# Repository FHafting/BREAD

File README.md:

# BREAD
This project is fully documented in the paper: Shane Oberloier, Nicholas G. Whisman, Finn Hafting, Joshua M. Pearce, Open Source Framework for a Broadly Expandable and Reconfigurable Data Acquisition and Automation Device (BREAD), ''HardwareX'', 2023, e00467, https://doi.org/10.1016/j.ohx.2023.e00467.

All case designs can be found on Onshape: https://cad.onshape.com/documents/f4c13a5c0b1f8d88ed1f5752/w/29d0c0346ddaeb06e16ff42f/e/1077373224ada363d171e3fe?renderMode=0&uiState=65d3aad45b82c32cb51ae4c9

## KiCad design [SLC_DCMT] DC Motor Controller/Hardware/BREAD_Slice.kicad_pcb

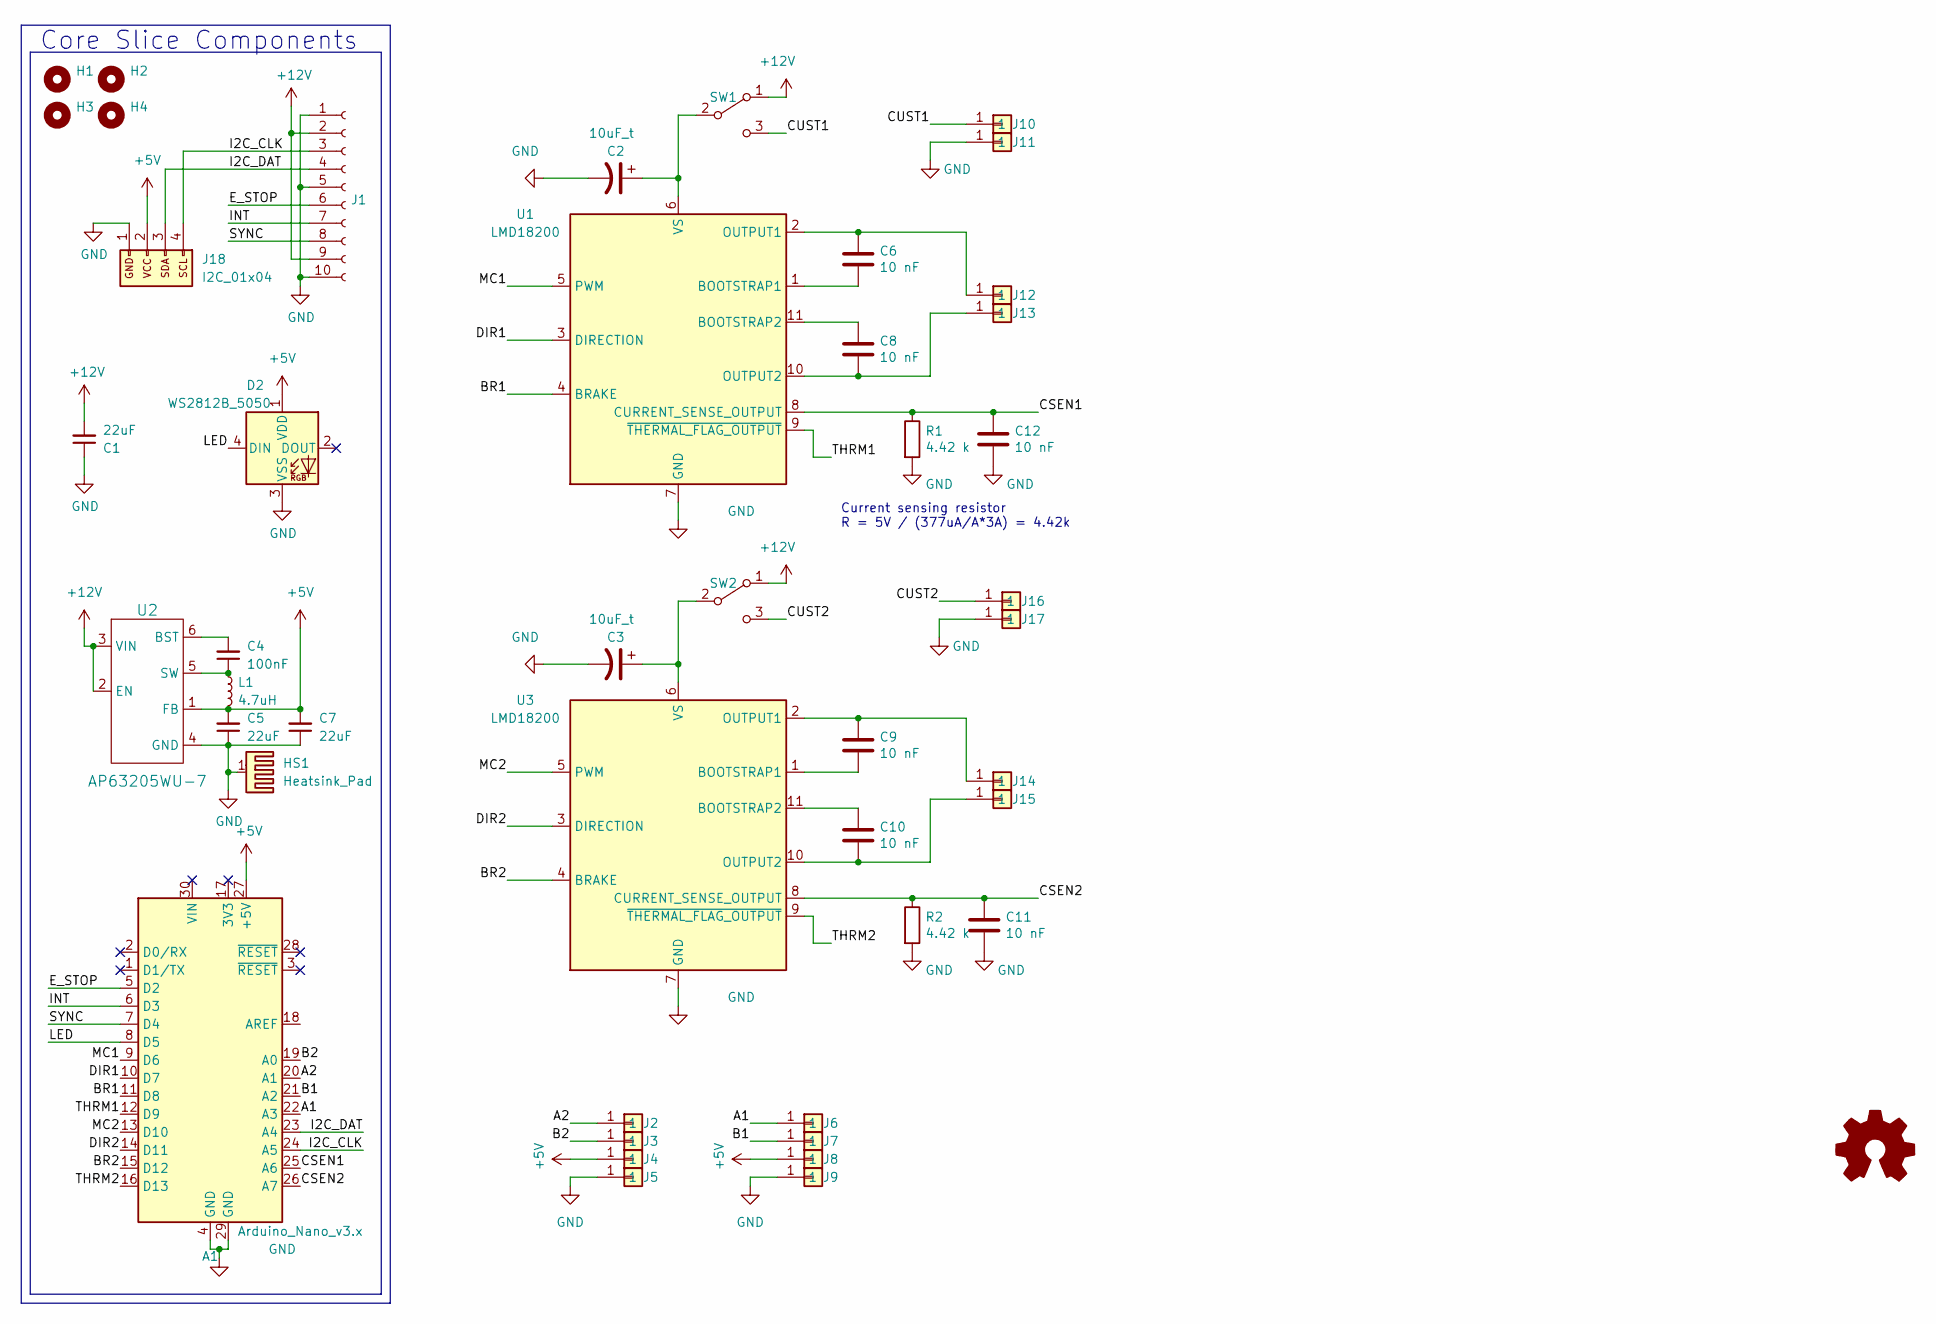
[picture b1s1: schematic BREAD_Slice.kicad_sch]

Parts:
A1: Arduino_Nano_v3.x; Arduino_Nano
C1, C5, C7: 22uF; C_1206_3216Metric
C2, C3: 10uF_t; C_1206_3216Metric; Part # T491C106K025AT
C4: 100nF; C_1206_3216Metric
C6, C8, C9, C10, C11, C12: 10 nF; C_1206_3216Metric_Pad1.33x1.80mm_HandSolder
D2: WS2812B_5050; WS2812-5050-4PIN
H1, H2, H3, H4: MountingHole; MountingHole_5mm
HS1: Heatsink_Pad; Thermal Pad
J1: Conn_01x10_Female; PinSocket_1x10_P2.54mm_Horizontal
J2, J3, J4, J5, J7, J8, J9: Term_PressFit_Phoenix_Contact; Term_PressFit_3.5mm_H_PC
J6: Term_PressFit_Phoenix_Contact; Term_PressFit_3.5mm_H_ENDCAP_PC
J10, J11, J13, J15, J16, J17: Term_PressFit_Phoenix_Contact; Term_PressFit_5mm_H_PC
J12, J14: Term_PressFit_Phoenix_Contact; Term_PressFit_5mm_H_ENDCAP_PC
J18: I2C_01x04; JST_SH_SM04B-SRSS-TB_1x04-1MP_P1.00mm_Horizontal
L1: 4.7uH; L_1210_3225Metric
Logo1: Logo_Open_Hardware_Small; OSHW-Symbol_6.7x6mm_SilkScreen
R1, R2: 4.42 k; R_1206_3216Metric_Pad1.30x1.75mm_HandSolder
SW1, SW2: SW_SPDT; L102011MS02Q
U1, U3: LMD18200; TO-220-11_P3.4x5.08mm_StaggerOdd_Lead4.85mm_Vertical
U2: AP63205WU-7; TSOT-23-6

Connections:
+5V: A1.27 (+5V), C5.2, C7.2, D2.1 (VDD), J4.1, J8.1, J18.2, L1.2, U2.1 (FB)
+12V: C1.2, J1.2, J1.9, SW1.1 (A), SW2.1 (A), U2.2 (EN), U2.3 (VIN)
/A1: A1.22 (A3), J6.1
/A2: A1.20 (A1), J2.1
/B1: A1.21 (A2), J7.1
/B2: A1.19 (A0), J3.1
/BR1: A1.11 (D8), U1.4 (BRAKE)
/BR2: A1.15 (D12), U3.4 (BRAKE)
/CSEN1: A1.25 (A6), C12.1, R1.1, U1.8 (CURRENT_SENSE_OUTPUT)
/CSEN2: A1.26 (A7), C11.1, R2.1, U3.8 (CURRENT_SENSE_OUTPUT)
/CUST1: J10.1, SW1.3 (C)
/CUST2: J16.1, SW2.3 (C)
/DIR1: A1.10 (D7), U1.3 (DIRECTION)
/DIR2: A1.14 (D11), U3.3 (DIRECTION)
/E_STOP: A1.5 (D2), J1.6
/I2C_CLK: A1.24 (A5), J1.3, J18.4
/I2C_DAT: A1.23 (A4), J1.4, J18.3
/INT: A1.6 (D3), J1.7
/LED: A1.8 (D5), D2.4 (DIN)
/MC1: A1.9 (D6), U1.5 (PWM)
/MC2: A1.13 (D10), U3.5 (PWM)
/SYNC: A1.7 (D4), J1.8
/THRM1: A1.12 (D9), U1.9 (~THERMAL_FLAG_OUTPUT)
/THRM2: A1.16 (D13), U3.9 (~THERMAL_FLAG_OUTPUT)
GND: A1.4 (GND), A1.29 (GND), C1.1, C2.2, C3.2, C5.1, C7.1, C11.2, C12.2, D2.3 (VSS), HS1.1, J1.1, J1.5, J1.10, J5.1, J9.1, J11.1, J17.1, J18.1, R1.2, R2.2, U1.7 (GND), U2.4 (GND), U3.7 (GND)
unnamed: C2.1, SW1.2 (B), U1.6 (VS)
unnamed: C3.1, SW2.2 (B), U3.6 (VS)
unnamed: C6.2, U1.1 (BOOTSTRAP1)
unnamed: C8.1, U1.11 (BOOTSTRAP2)
unnamed: C6.1, J12.1, U1.2 (OUTPUT1)
unnamed: C8.2, J13.1, U1.10 (OUTPUT2)
unnamed: C4.2, U2.6 (BST)
unnamed: C4.1, L1.1, U2.5 (SW)
unnamed: C9.2, U3.1 (BOOTSTRAP1)
unnamed: C10.1, U3.11 (BOOTSTRAP2)
unnamed: C9.1, J14.1, U3.2 (OUTPUT1)
unnamed: C10.2, J15.1, U3.10 (OUTPUT2)

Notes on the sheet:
Current sensing resistor R = 5V / (377uA/A*3A) = 4.42k
Core Slice Components

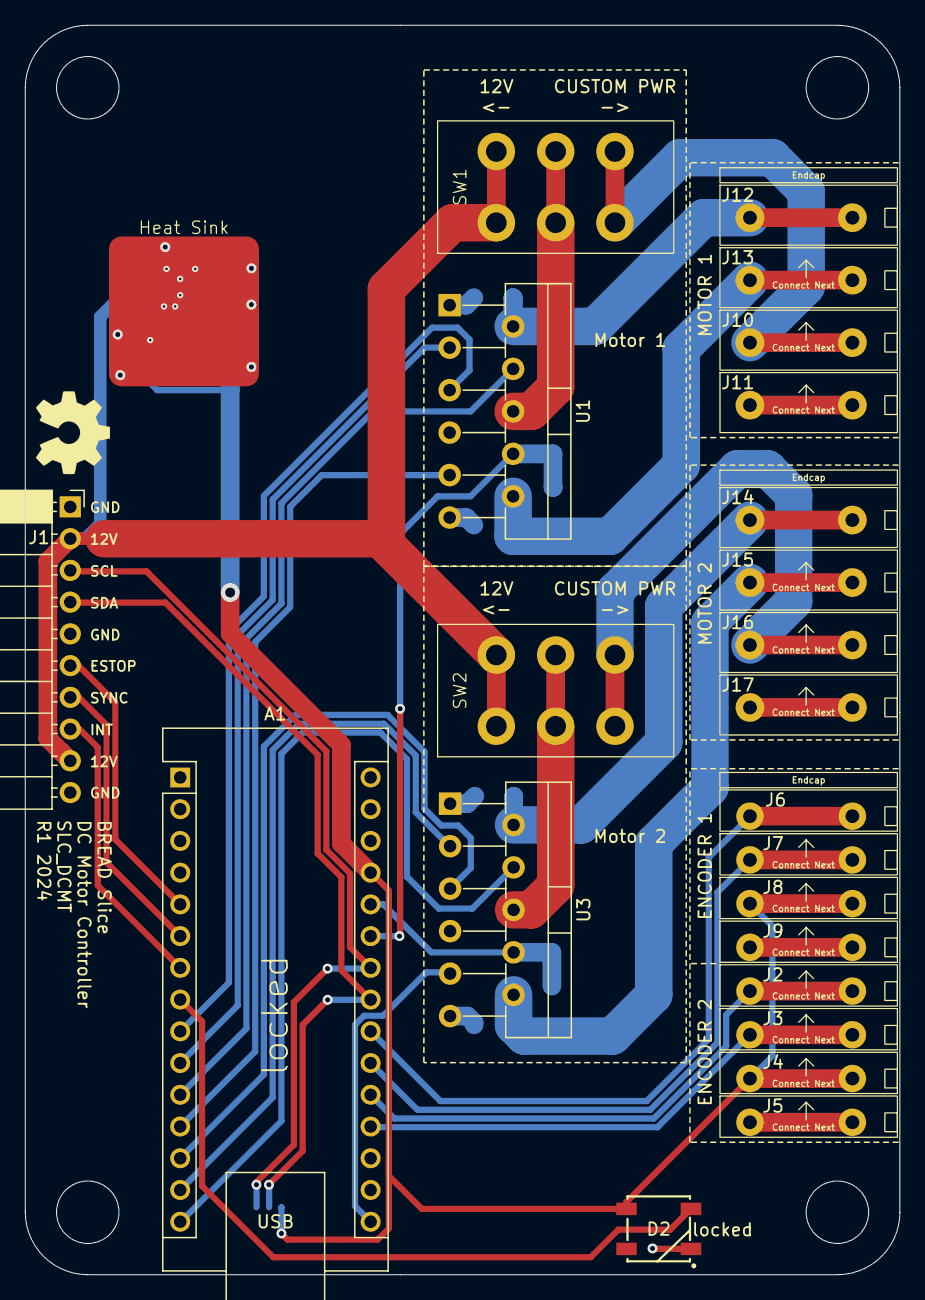
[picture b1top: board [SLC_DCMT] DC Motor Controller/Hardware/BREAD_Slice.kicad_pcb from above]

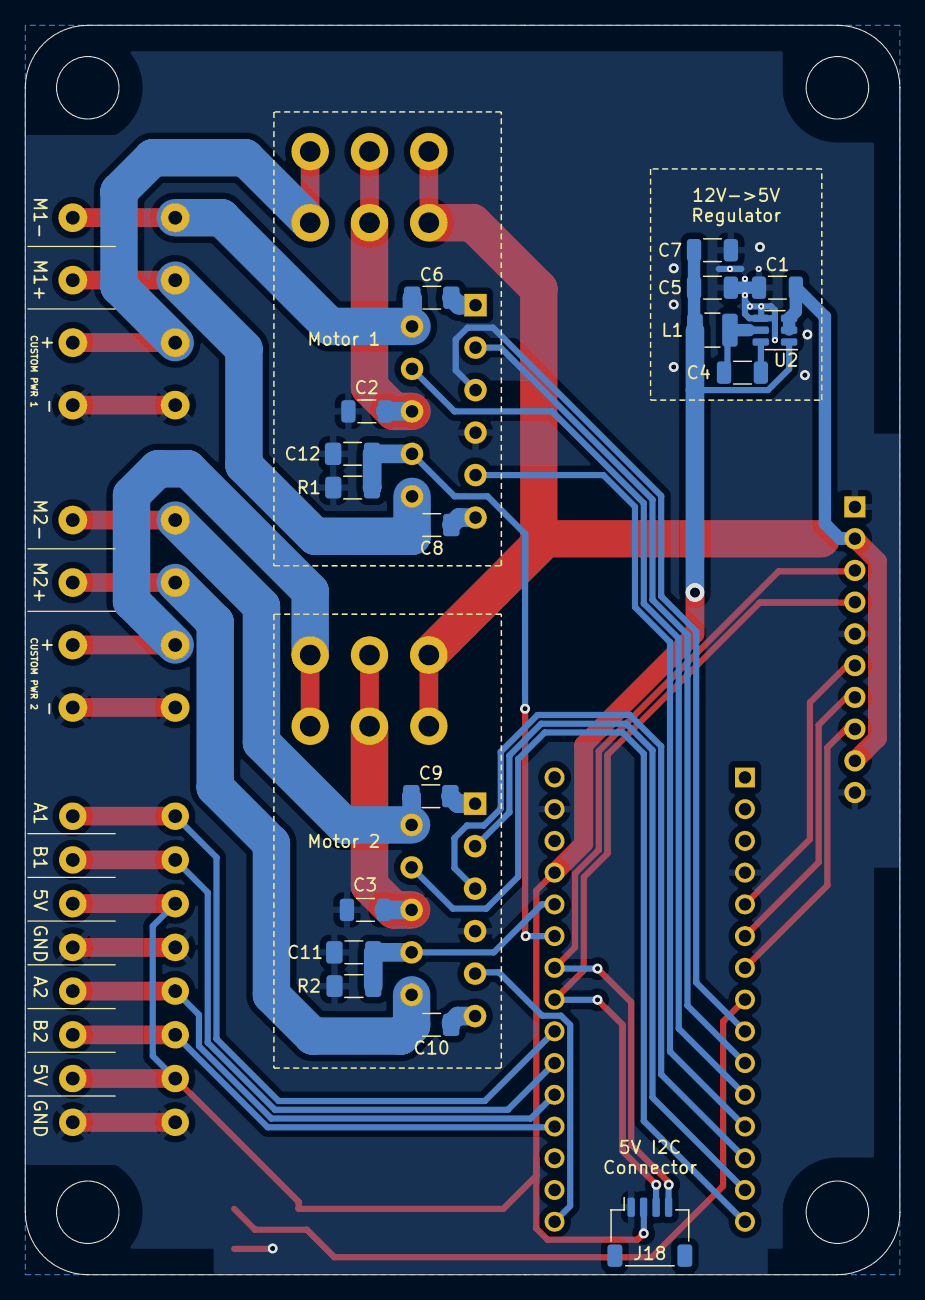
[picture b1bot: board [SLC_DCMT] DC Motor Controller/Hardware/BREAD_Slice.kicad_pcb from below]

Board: 2 copper layers, 70.0 x 100.0 mm, 46 parts (17 on the bottom side), 37 nets.

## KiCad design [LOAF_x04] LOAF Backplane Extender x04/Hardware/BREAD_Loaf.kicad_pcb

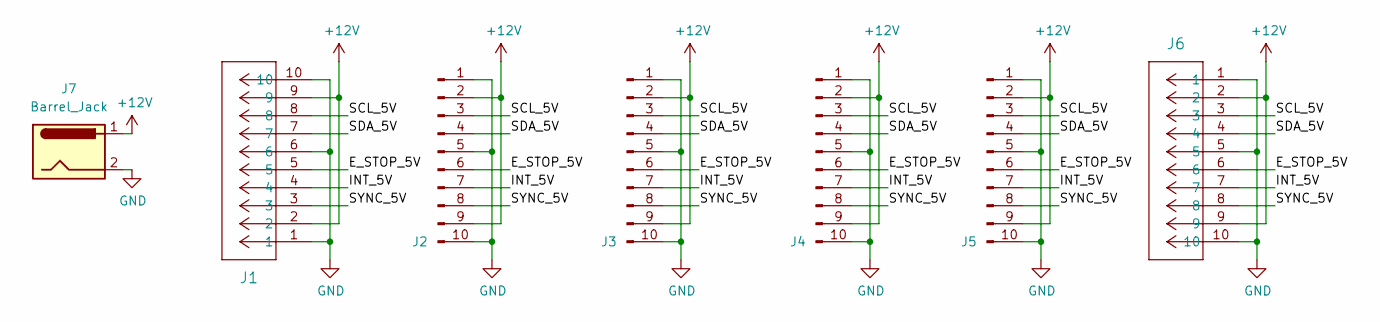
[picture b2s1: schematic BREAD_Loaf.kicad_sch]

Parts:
J1: PPPC101LGBN-RC; 1x10 RA Male Header 2.54mm Pitch
J2, J3, J4, J5: Conn_01x10_Male; BREAD 10-Pin Connector
J6: PPPC101LGBN-RC; PinSocket_1x10_P2.54mm_Horizontal
J7: Barrel_Jack; BarrelJack_CUI_PJ-063AH_Horizontal

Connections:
+12V: J1.2, J1.9, J2.2, J2.9, J3.2, J3.9, J4.2, J4.9, J5.2, J5.9, J6.2, J6.9, J7.1
/E_STOP_5V: J1.5, J2.6, J3.6, J4.6, J5.6, J6.6
/INT_5V: J1.4, J2.7, J3.7, J4.7, J5.7, J6.7
/SCL_5V: J1.8, J2.3, J3.3, J4.3, J5.3, J6.3
/SDA_5V: J1.7, J2.4, J3.4, J4.4, J5.4, J6.4
/SYNC_5V: J1.3, J2.8, J3.8, J4.8, J5.8, J6.8
GND: J1.1, J1.6, J1.10, J2.1, J2.5, J2.10, J3.1, J3.5, J3.10, J4.1, J4.5, J4.10, J5.1, J5.5, J5.10, J6.1, J6.5, J6.10, J7.2

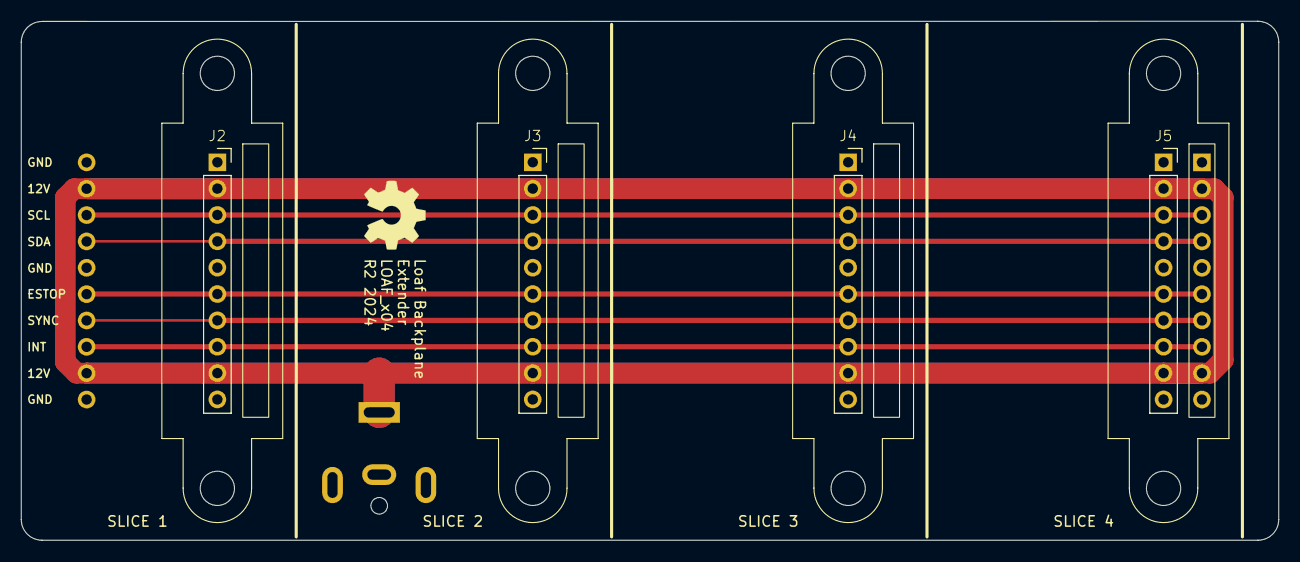
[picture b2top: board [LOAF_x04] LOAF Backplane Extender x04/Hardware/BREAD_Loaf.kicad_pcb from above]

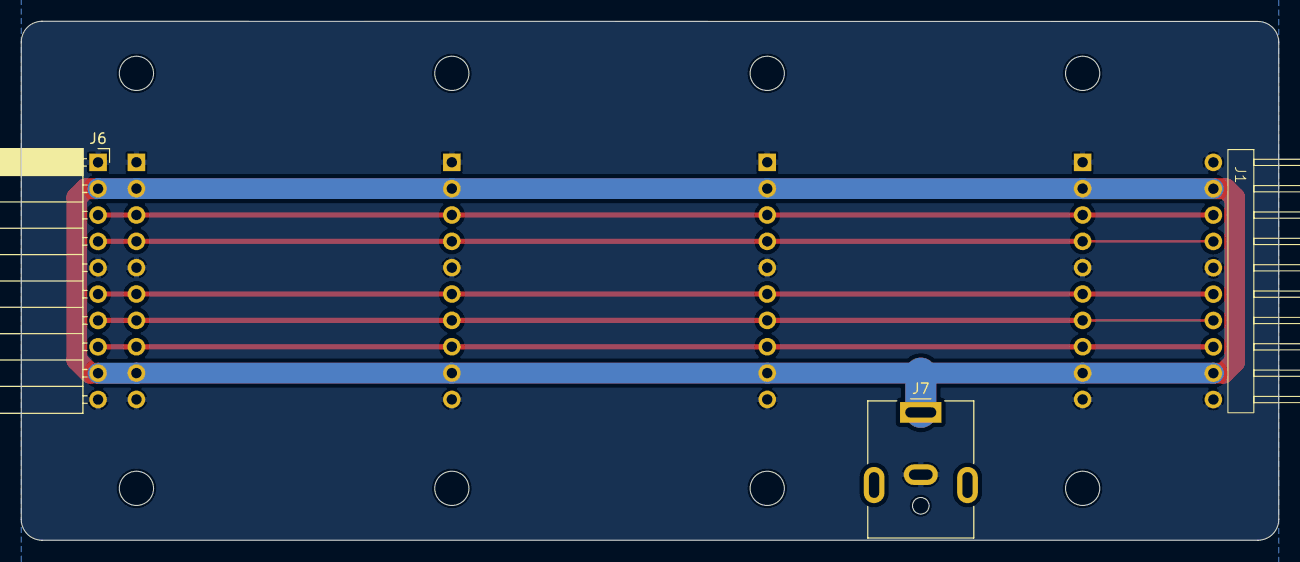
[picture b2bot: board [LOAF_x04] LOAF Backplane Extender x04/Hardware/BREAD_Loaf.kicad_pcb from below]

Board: 2 copper layers, 121.2 x 50.0 mm, 8 parts (3 on the bottom side), 7 nets.

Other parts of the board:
Logo1: Logo_Open_Hardware_Small; OSHW-Symbol_6.7x6mm_SilkScreen

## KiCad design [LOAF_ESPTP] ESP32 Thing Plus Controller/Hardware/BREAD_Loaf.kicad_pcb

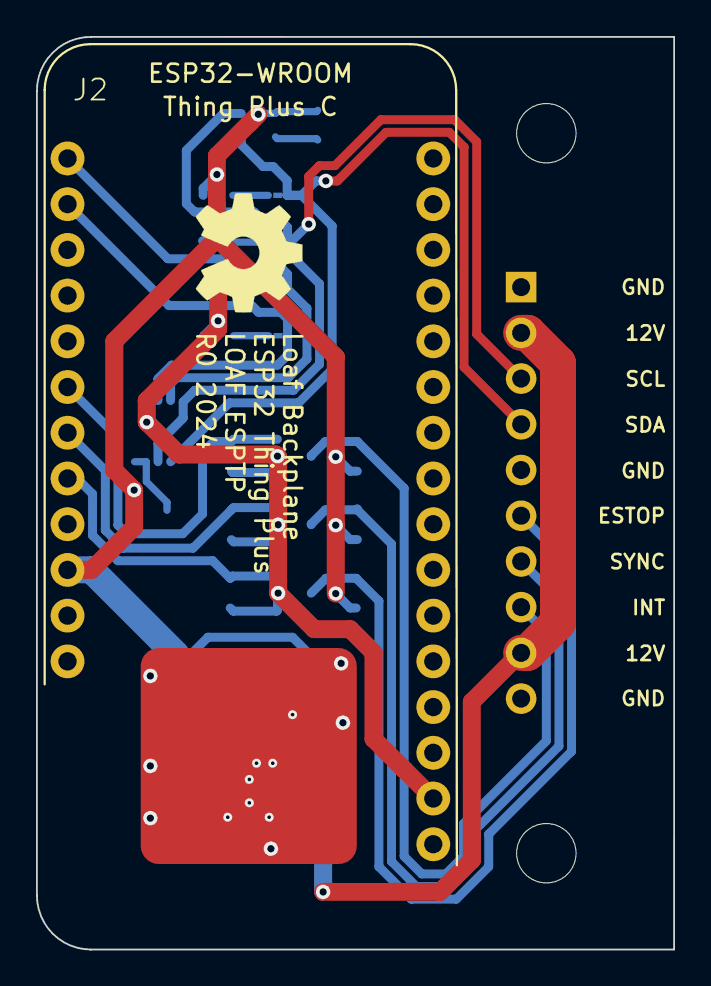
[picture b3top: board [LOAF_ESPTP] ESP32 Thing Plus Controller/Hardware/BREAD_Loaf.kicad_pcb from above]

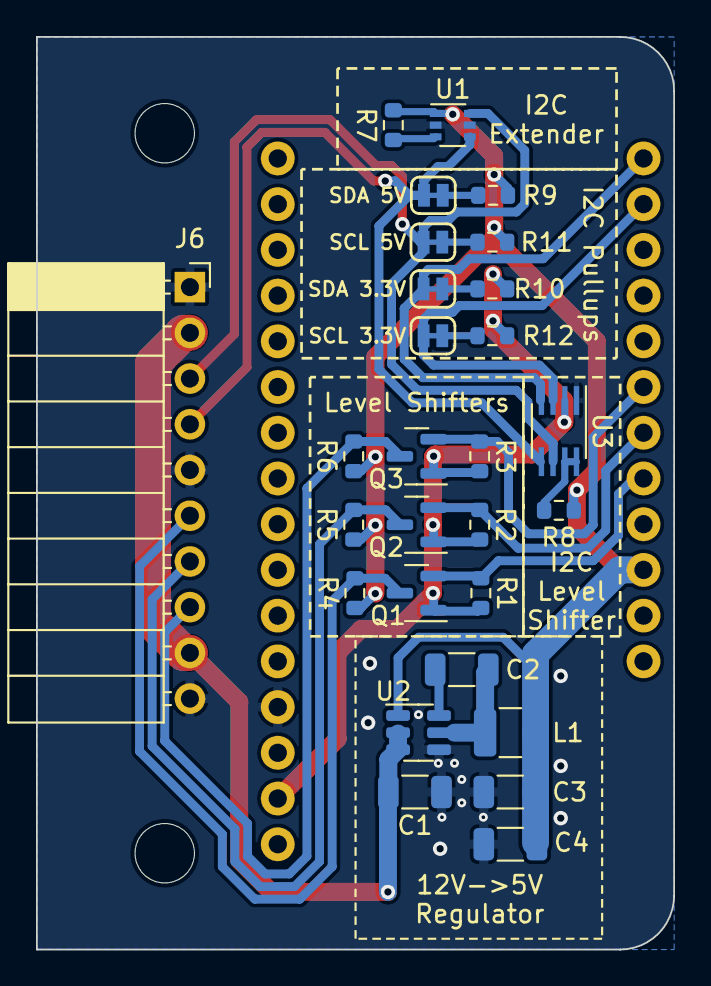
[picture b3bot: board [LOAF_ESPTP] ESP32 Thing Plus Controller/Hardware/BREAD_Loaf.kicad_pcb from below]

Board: 2 copper layers, 35.4 x 50.7 mm, 33 parts (28 on the bottom side), 22 nets.

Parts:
C1, C3, C4: 22uF; C_1206_3216Metric
C2: 100nF; C_1206_3216Metric
HS1: Heatsink_Pad; Thermal Pad
J2: THING_PLUS_LOGICAL; ESP_THING_PLUS
J6: PPPC101LGBN-RC; PinSocket_1x10_P2.54mm_Horizontal
JP1, JP2, JP3, JP4: SMT-JUMPER_2_NC_TRACE_SILK
L1: 4.7uH; L_1210_3225Metric
Logo1: Logo_Open_Hardware_Small; OSHW-Symbol_6.7x6mm_SilkScreen
Q1, Q2, Q3: BSS138; SOT-23
R1, R2, R3, R4, R5, R6, R7: 10k; R_0603_1608Metric
R8: 200k; R_0603_1608Metric
R9, R11: 4.7k; R_0603_1608Metric
R10, R12: 2.2k; R_0603_1608Metric
ST1, ST2: Stand_off; STAND-OFF
U1: LTC4311ISC6-TRMPBF; SOT-363_SC-70-6
U2: AP63205WU-7; TSOT-23-6
U3: PCA9306; SSOP-8_2.95x2.8mm_P0.65mm

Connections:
+3.3V: J2.27 (3.3V), Q1.1 (G), Q2.1 (G), Q3.1 (G), R1.2, R2.2, R3.2, R10.1, R12.1, U3.2 (VREF1)
+5V: C3.2, C4.2, J2.10 (V_USB), L1.2, R4.2, R5.2, R6.2, R7.1, R8.2, R9.1, R11.1, U1.1 (VCC), U2.1 (FB)
+12V: C1.2, J6.2, J6.9, U2.2 (EN), U2.3 (VIN)
/E_STOP_3.3V: J2.8 (GPIO1), Q1.2 (S), R1.1
/E_STOP_5V: J6.6, Q1.3 (D), R4.1
/INT_3.3V: J2.7 (GPIO2), Q2.2 (S), R2.1
/INT_5V: J6.7, Q2.3 (D), R5.1
/SCL_3.3V: J2.2 (SCL), JP4.2 (B), U3.3 (SCL1)
/SCL_5V: J6.3, JP2.2 (B), U1.6 (BUS1), U3.6 (SCL2)
/SDA_3.3V: J2.1 (SDA), JP3.2 (B), U3.4 (SDA1)
/SDA_5V: J6.4, JP1.2 (B), U1.4 (BUS2), U3.5 (SDA2)
/SYNC_3.3V: J2.6 (GPIO3), Q3.2 (S), R3.1
/SYNC_5V: J6.8, Q3.3 (D), R6.1
GND: C1.1, C3.1, C4.1, HS1.1, J2.25 (GND), J6.1, J6.5, J6.10, U1.2 (GND), U1.5 (GND), U2.4 (GND), U3.1 (GND)
unnamed: JP1.1 (A), R9.2
unnamed: JP2.1 (A), R11.2
unnamed: JP3.1 (A), R10.2
unnamed: JP4.1 (A), R12.2
unnamed: R7.2, U1.3 (ENABLE)
unnamed: C2.2, U2.6 (BST)
unnamed: C2.1, L1.1, U2.5 (SW)
unnamed: R8.1, U3.7 (VREF2), U3.8 (EN)

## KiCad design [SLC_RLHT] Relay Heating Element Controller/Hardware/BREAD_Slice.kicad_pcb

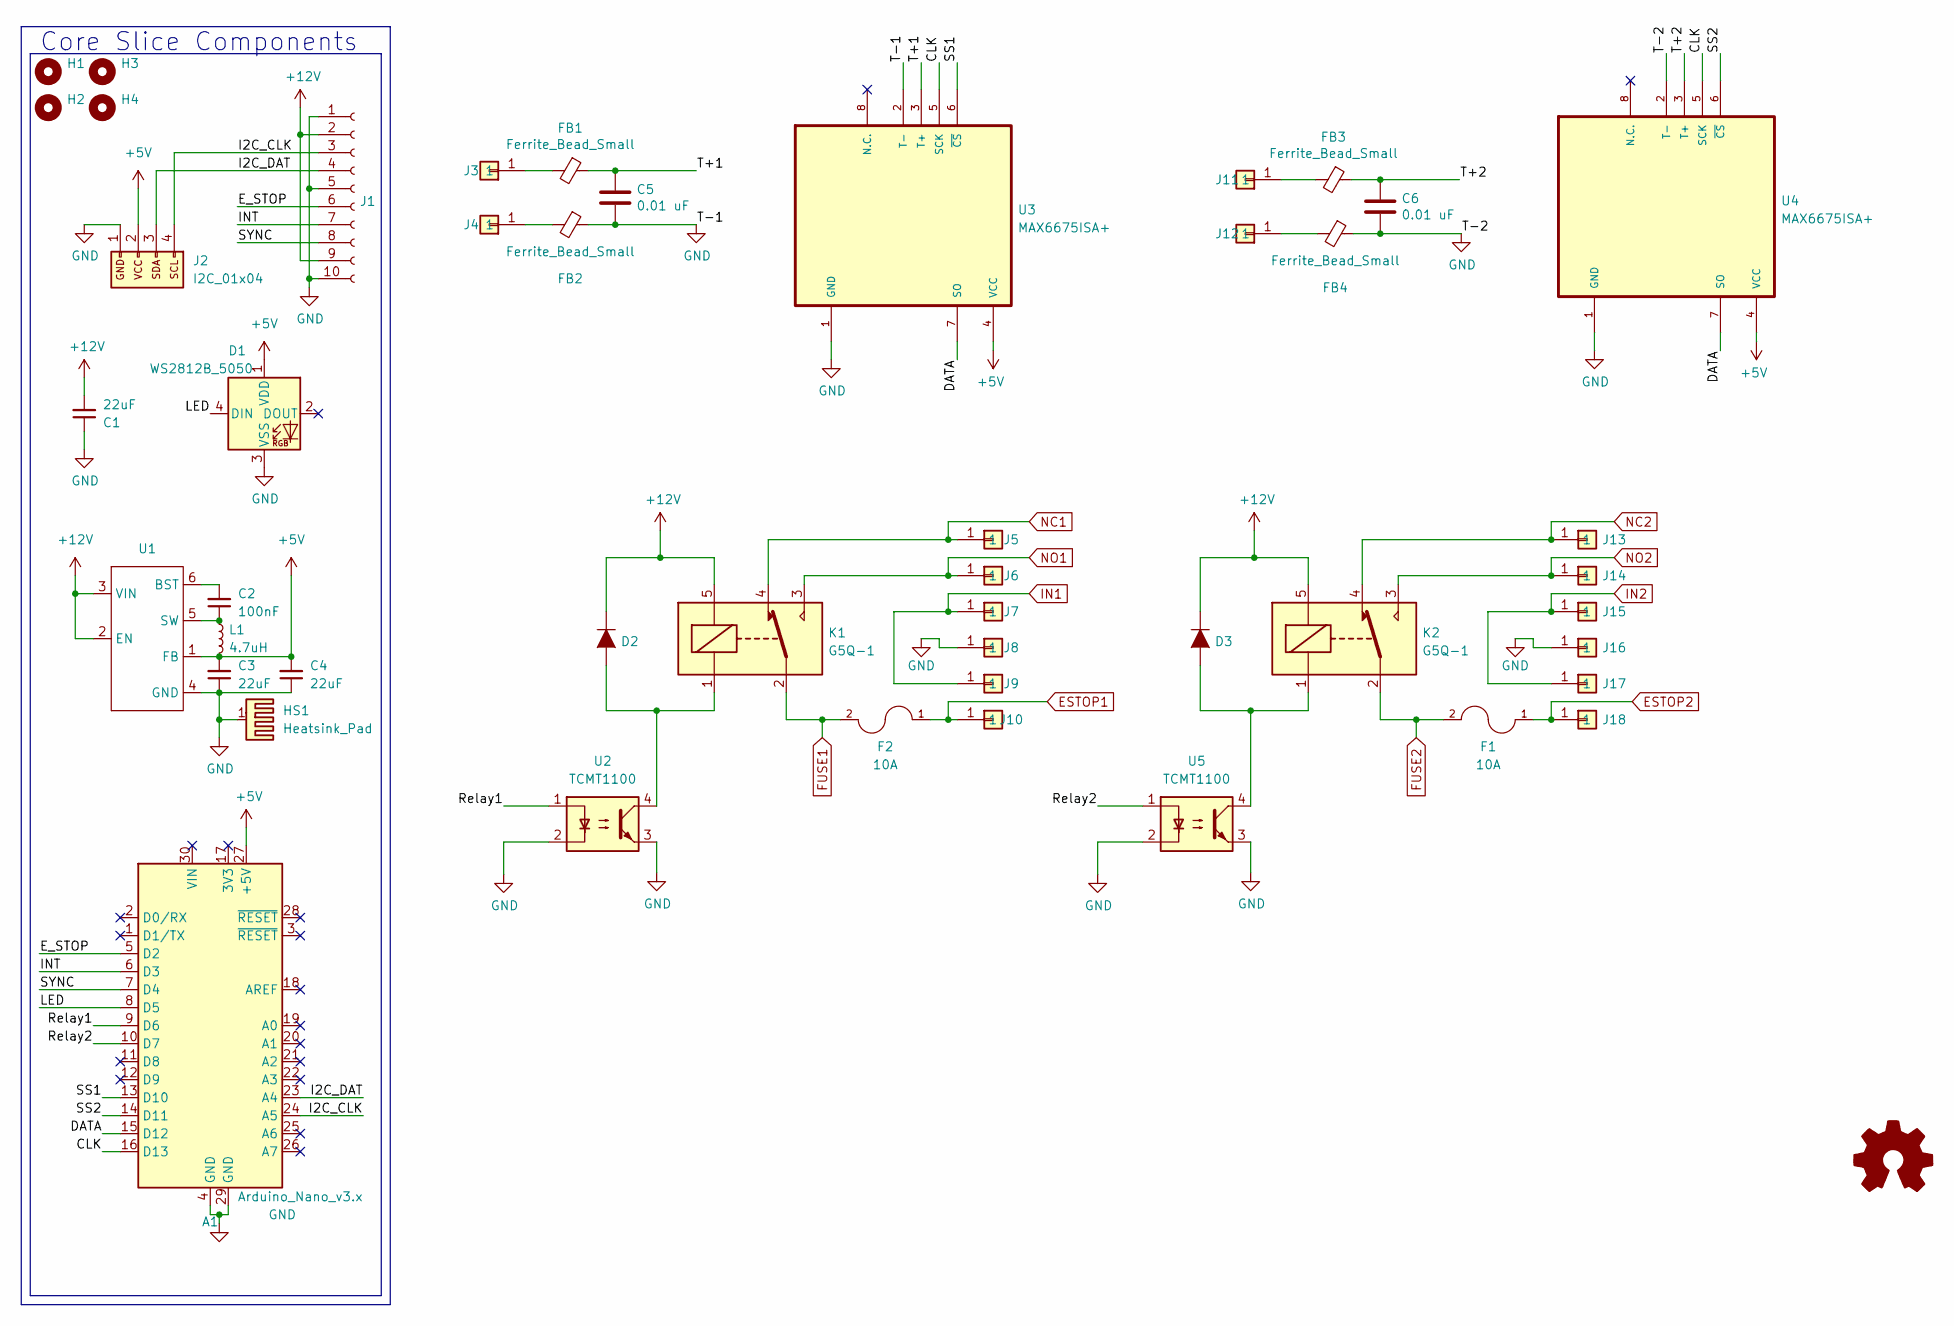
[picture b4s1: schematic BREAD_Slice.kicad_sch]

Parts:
A1: Arduino_Nano_v3.x; Arduino_Nano
C1, C3, C4: 22uF; C_1206_3216Metric
C2: 100nF; C_1206_3216Metric
C5, C6: 0.01 uF; C_1206_3216Metric
D1: WS2812B_5050; WS2812-5050-4PIN
D2, D3: General_Purpose_Diode; D_DO-35_SOD27_P7.62mm_Horizontal; Part # 1N914BWS
F1, F2: 10A; Glass Fuse Clip 5x20MM; Part # 3522-2
FB1, FB2, FB3, FB4: Ferrite_Bead_Small; R_1206_3216Metric
H1, H2, H3, H4: MountingHole; MountingHole_5mm
HS1: Heatsink_Pad; Thermal Pad
J1: Conn_01x10_Female; PinSocket_1x10_P2.54mm_Horizontal
J2: I2C_01x04; JST_SH_SM04B-SRSS-TB_1x04-1MP_P1.00mm_Horizontal
J3, J11, J12: Term_PressFit_Phoenix_Contact; Term_PressFit_3.5mm_H_PC
J4: Term_PressFit_Phoenix_Contact; Term_PressFit_3.5mm_H_ENDCAP_PC
J5: Term_PressFit_Phoenix_Contact; Term_PressFit_5mm_H_ENDCAP_PC_HVRELAY
J6, J7, J8, J9, J10, J13, J14, J15, J16, J17, J18: Term_PressFit_Phoenix_Contact; Term_PressFit_5mm_H_PC_HVRELAY
K1, K2: G5Q-1; Relay_SPDT_Omron-G5Q-1
L1: 4.7uH; L_1210_3225Metric
U1: TSOT-23-6
U2, U5: TCMT1100; SOP-4_4.4x2.6mm_P1.27mm
U3, U4: MAX6675ISA+; SOIC127P600X175-8N

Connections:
+5V: A1.27 (+5V), C3.2, C4.2, D1.1 (VDD), J2.2, L1.2, U1.1 (FB), U3.4 (VCC), U4.4 (VCC)
+12V: C1.2, D2.1 (K), D3.1 (K), J1.2, J1.9, K1.5, K2.5, U1.2 (EN), U1.3 (VIN)
/CLK: A1.16 (D13), U3.5 (SCK), U4.5 (SCK)
/DATA: A1.15 (D12), U3.7 (SO), U4.7 (SO)
/E_STOP: A1.5 (D2), J1.6
/I2C_CLK: A1.24 (A5), J1.3, J2.4
/I2C_DAT: A1.23 (A4), J1.4, J2.3
/INT: A1.6 (D3), J1.7
/LED: A1.8 (D5), D1.4 (DIN)
/Relay1: A1.9 (D6), U2.1
/Relay2: A1.10 (D7), U5.1
/SS1: A1.13 (D10), U3.6 (~CS)
/SS2: A1.14 (D11), U4.6 (~CS)
/SYNC: A1.7 (D4), J1.8
/T+1: C5.1, FB1.1, U3.3 (T+)
/T+2: C6.1, FB3.1, U4.3 (T+)
ESTOP1: F2.1, J10.1
ESTOP2: F1.1, J18.1
FUSE1: F2.2, K1.2
FUSE2: F1.2, K2.2
GND: A1.4 (GND), A1.29 (GND), C1.1, C3.1, C4.1, C5.2, C6.2, D1.3 (VSS), FB2.1, FB4.1, HS1.1, J1.1, J1.5, J1.10, J2.1, J8.1, J16.1, U1.4 (GND), U2.2, U2.3, U3.1 (GND), U3.2 (T-), U4.1 (GND), U4.2 (T-), U5.2, U5.3
IN1: J7.1, J9.1
IN2: J15.1, J17.1
NC1: J5.1, K1.4
NC2: J13.1, K2.4
NO1: J6.1, K1.3
NO2: J14.1, K2.3
unnamed: D2.2 (A), K1.1, U2.4
unnamed: D3.2 (A), K2.1, U5.4
unnamed: FB1.2, J3.1
unnamed: FB2.2, J4.1
unnamed: FB3.2, J11.1
unnamed: FB4.2, J12.1
unnamed: C2.2, U1.6 (BST)
unnamed: C2.1, L1.1, U1.5 (SW)

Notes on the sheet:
Core Slice Components

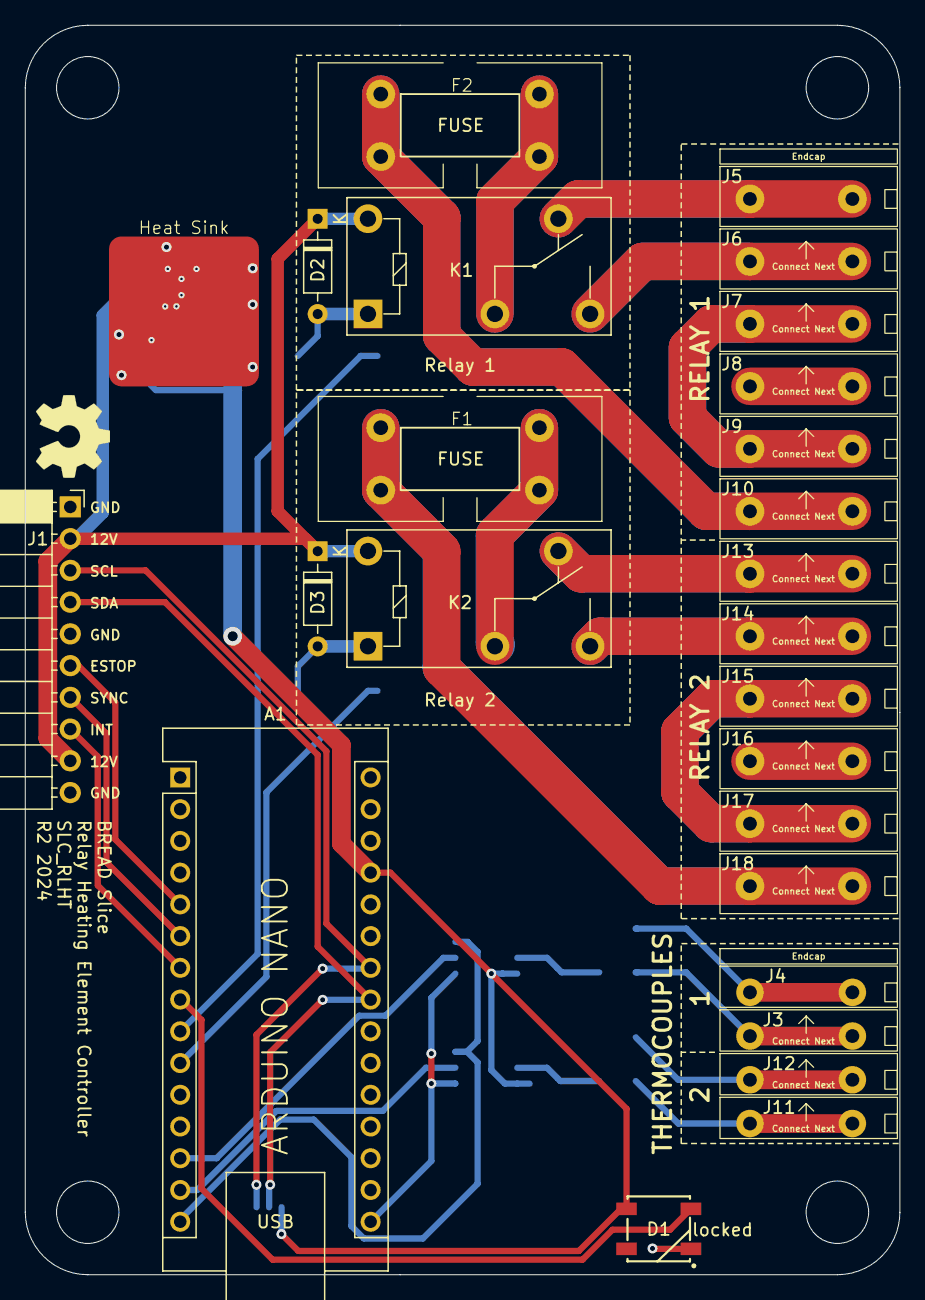
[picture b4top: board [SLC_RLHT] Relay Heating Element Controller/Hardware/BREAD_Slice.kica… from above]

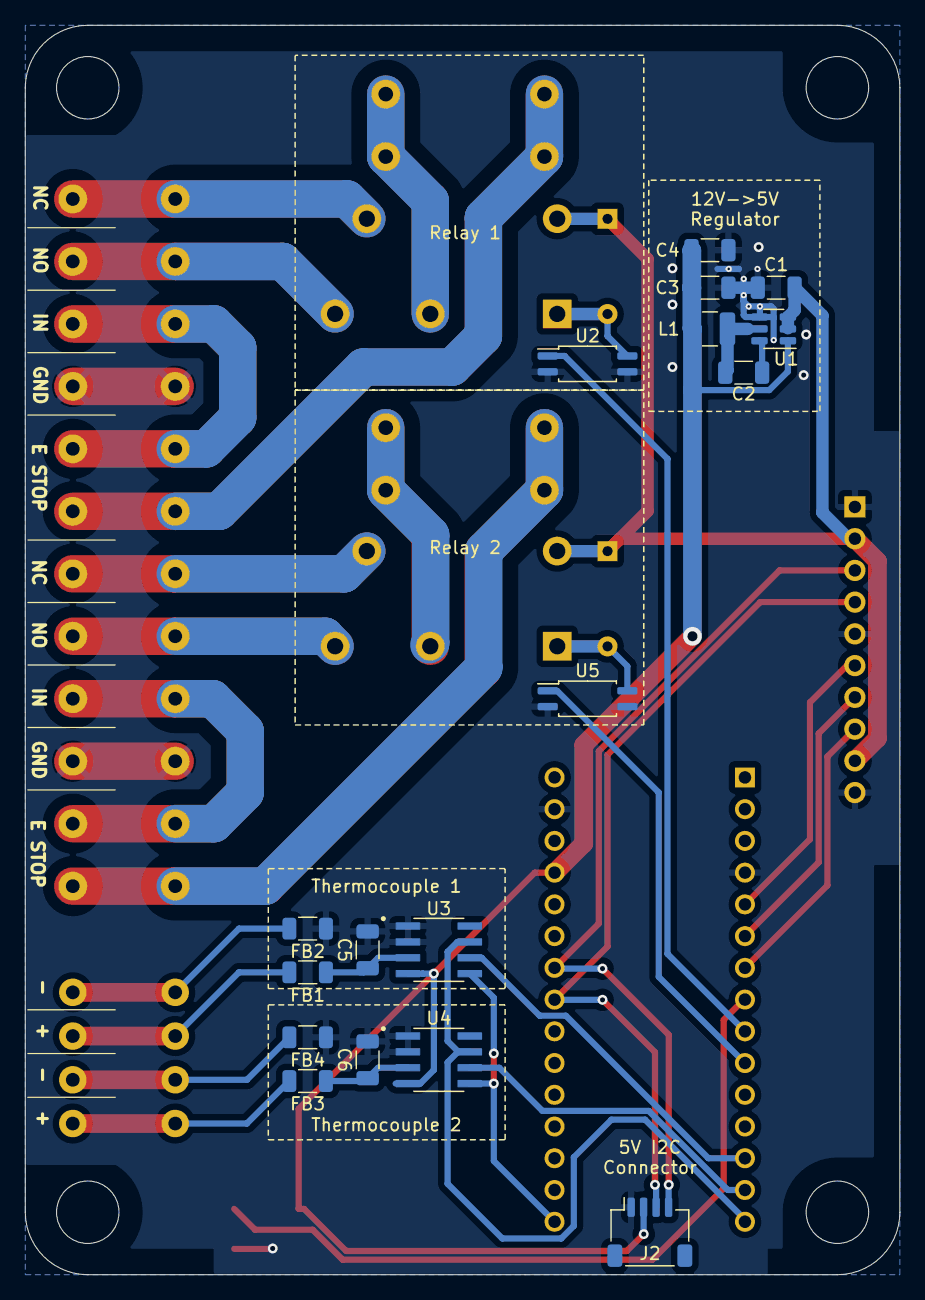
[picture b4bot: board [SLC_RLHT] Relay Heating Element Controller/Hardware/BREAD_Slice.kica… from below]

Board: 2 copper layers, 70.0 x 100.0 mm, 48 parts (17 on the bottom side), 35 nets.

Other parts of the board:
Logo1: Logo_Open_Hardware_Small; OSHW-Symbol_6.7x6mm_SilkScreen

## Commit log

2024-02-13 Added SLC_RLHT R1 hardware files
2024-02-16 Added BOM for RLHT_R2
2024-02-17 Updated RLHT BOM
2024-02-17 Added SLC_DCMT_R1 files
2024-02-18 Added LOAF_ESPTP_R0 files
2024-02-18 Added LOAF_x04_R2 files
2024-02-19 Update README.md with Onshape Link
2024-02-20 Updated BOM for ESPTP and RLHT
2024-04-29 Updated DCMT pin connections
2024-06-28 Fixed polarity of external power input
